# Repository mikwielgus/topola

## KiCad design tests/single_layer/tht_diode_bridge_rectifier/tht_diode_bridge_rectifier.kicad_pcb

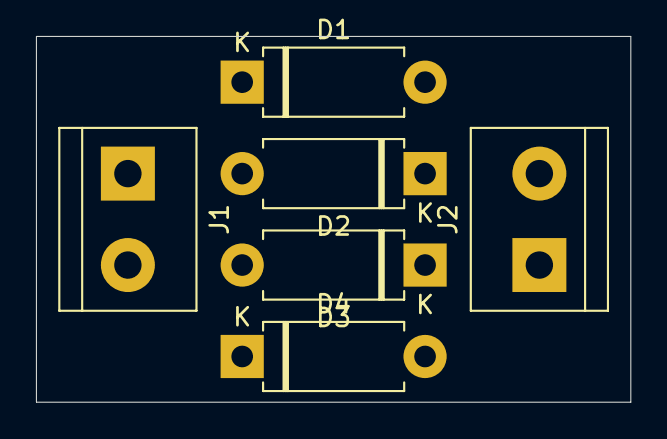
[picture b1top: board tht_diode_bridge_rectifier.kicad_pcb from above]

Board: 2 copper layers, 33.0 x 20.3 mm, 6 parts (0 on the bottom side), 4 nets, no tracks yet.

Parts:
D1, D2, D3, D4: D_45deg; D_DO-15_P10.16mm_Horizontal
J1, J2: Screw_Terminal_01x02; TerminalBlock_bornier-2_P5.08mm

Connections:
unnamed: D1.2 (A), D4.2 (A), J2.2
unnamed: D1.1 (K), D2.2 (A), J1.1
unnamed: D2.1 (K), D3.1 (K), J2.1
unnamed: D3.2 (A), D4.1 (K), J1.2

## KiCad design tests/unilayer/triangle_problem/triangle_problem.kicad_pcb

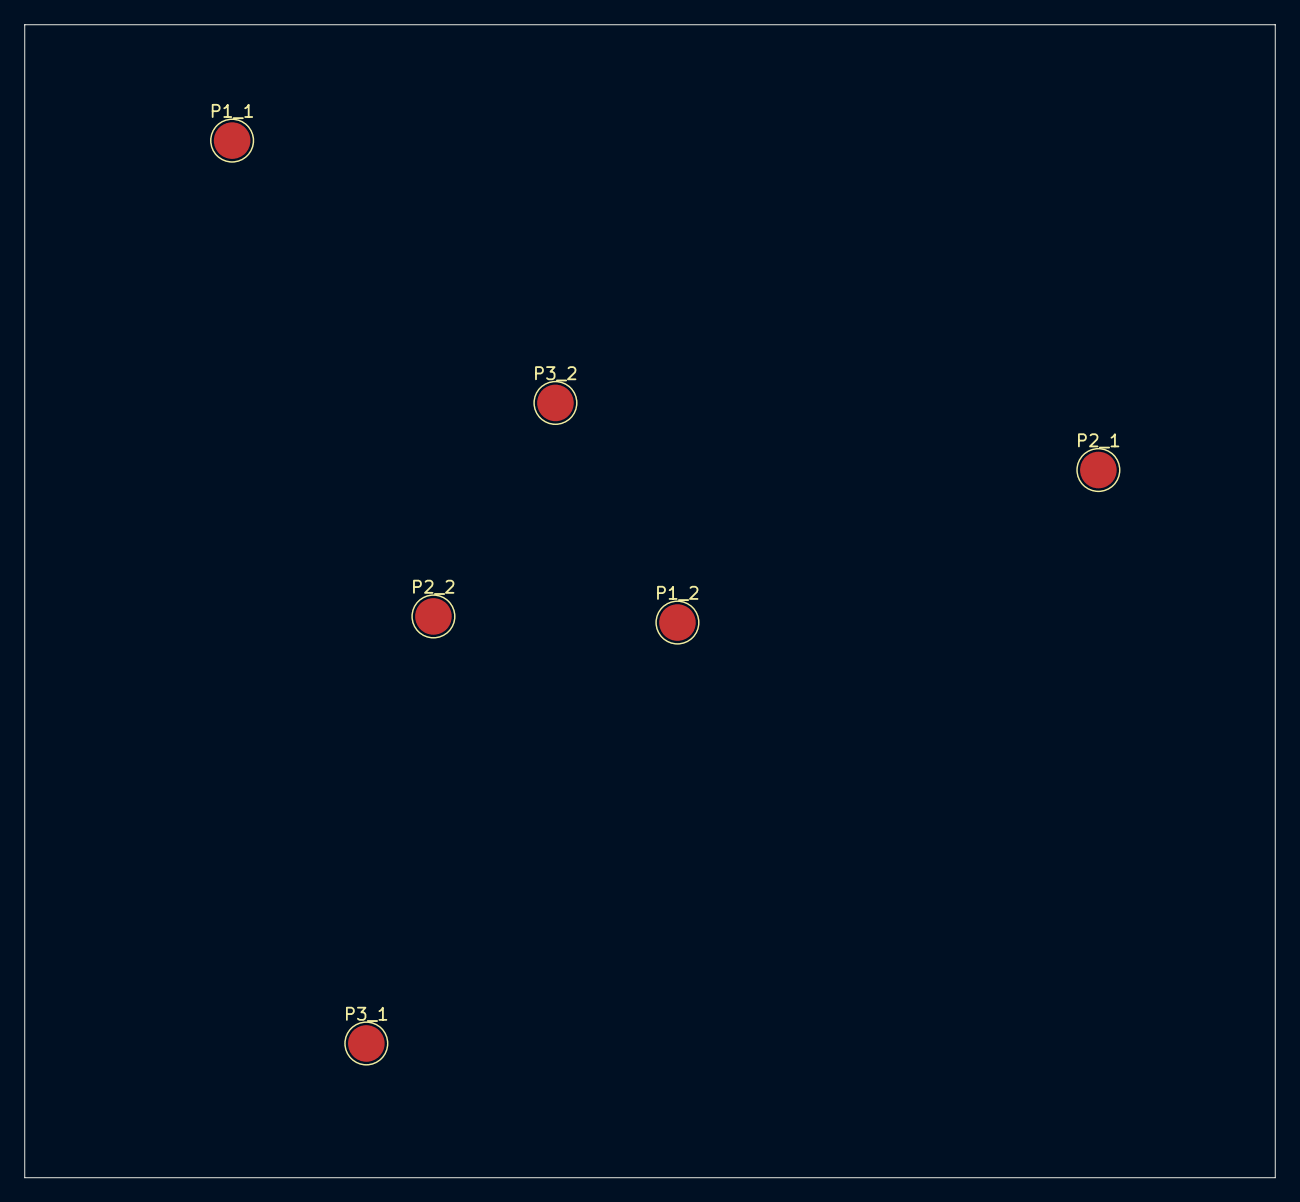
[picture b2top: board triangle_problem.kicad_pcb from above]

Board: 2 copper layers, 102.5 x 94.5 mm, 6 parts (0 on the bottom side), 3 nets, no tracks yet.

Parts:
P1_1, P1_2, P2_1, P2_2, P3_1, P3_2: TestPoint_Pad_D3.0mm

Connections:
1: P1_1.1, P1_2.1
2: P2_1.1, P2_2.1
3: P3_1.1, P3_2.1

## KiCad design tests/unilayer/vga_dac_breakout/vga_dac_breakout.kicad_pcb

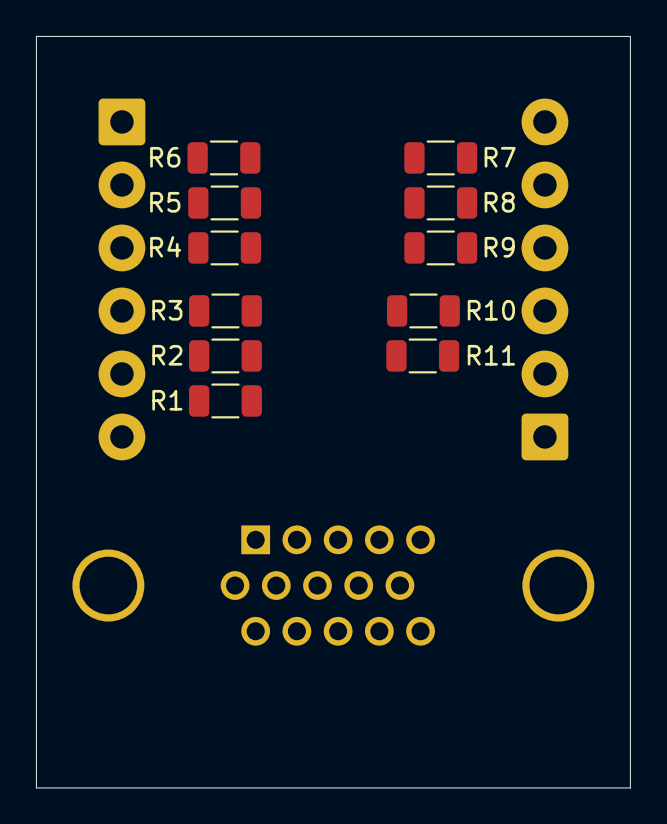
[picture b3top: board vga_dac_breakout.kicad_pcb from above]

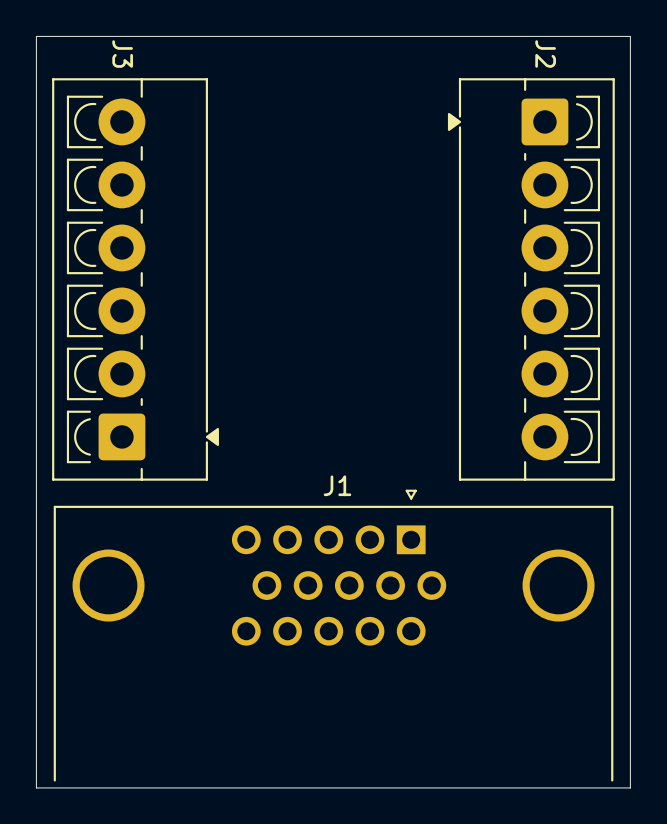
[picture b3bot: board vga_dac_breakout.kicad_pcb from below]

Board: 2 copper layers, 33.0 x 41.8 mm, 14 parts (3 on the bottom side), 17 nets, no tracks yet.

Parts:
J1: DE15_Socket_HighDensity_MountingHoles; DSUB-15-HD_Socket_Horizontal_P2.29x2.54mm_EdgePinOffset8.35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
J2, J3: Screw_Terminal_01x06; TerminalBlock_4Ucon_1x06_P3.50mm_Vertical
R1, R4, R7: 2K; R_1206_3216Metric
R2, R5, R8: 1K; R_1206_3216Metric
R3, R6, R9: 510; R_1206_3216Metric
R10, R11: 200; R_1206_3216Metric

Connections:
unnamed: J1.1, R1.1, R2.1, R3.1
unnamed: J1.2, R4.1, R5.1, R6.1
unnamed: J1.3, R7.1, R8.1, R9.1
unnamed: J1.13, R10.1
unnamed: J1.14, R11.1
unnamed: J2.1, R6.2
unnamed: J2.2, R5.2
unnamed: J2.3, R4.2
unnamed: J2.4, R3.2
unnamed: J2.5, R2.2
unnamed: J2.6, R1.2
unnamed: J1.0, J1.5, J1.6, J1.7, J1.8, J1.10, J3.1
unnamed: J3.2, R11.2
unnamed: J3.3, R10.2
unnamed: J3.4, R9.2
unnamed: J3.5, R8.2
unnamed: J3.6, R7.2
